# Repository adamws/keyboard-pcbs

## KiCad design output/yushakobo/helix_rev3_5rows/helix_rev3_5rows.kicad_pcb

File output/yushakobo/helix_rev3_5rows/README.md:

## yushakobo/helix_rev3_5rows

[layout](helix_rev3_5rows-kle.json) - [PCB](helix_rev3_5rows.kicad_pcb)

{:loading="lazy"}

[Open in keyboard-layout-editor](http://www.keyboard-layout-editor.com/##@@=0,0&=0,1&=0,2&=0,3&=0,4&=0,5&_x:2.25;&=5,5&=5,4&=5,3&=5,2&=5,1&_c=#aaaaaa;&=5,0;&@=1,0&_c=#cccccc;&=1,1&=1,2&=1,3&=1,4&=1,5&_x:2.25;&=6,5&=6,4&=6,3&=6,2&=6,1&_c=#aaaaaa;&=6,0;&@=2,0&_c=#cccccc;&=2,1&=2,2&=2,3&=2,4&=2,5&_x:2.25;&=7,5&=7,4&=7,3&=7,2&=7,1&=7,0;&@_c=#aaaaaa;&=3,0&_c=#cccccc;&=3,1&=3,2&=3,3&=3,4&=3,5&=3,6&_x:0.25;&=8,6&=8,5&=8,4&=8,3&=8,2&=8,1&_c=#aaaaaa;&=8,0;&@=4,0&=4,1&=4,2&=4,3&=4,4&=4,5&_c=#cccccc;&=4,6&_x:0.25;&=9,6&_c=#aaaaaa;&=9,5&=9,4&=9,3&=9,2&=9,1&=9,0)

{:loading="lazy"}

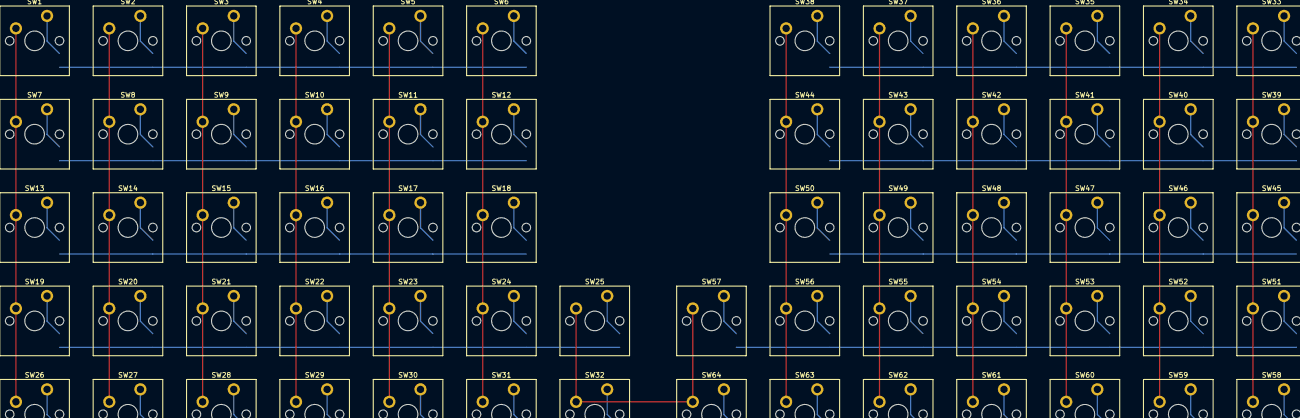
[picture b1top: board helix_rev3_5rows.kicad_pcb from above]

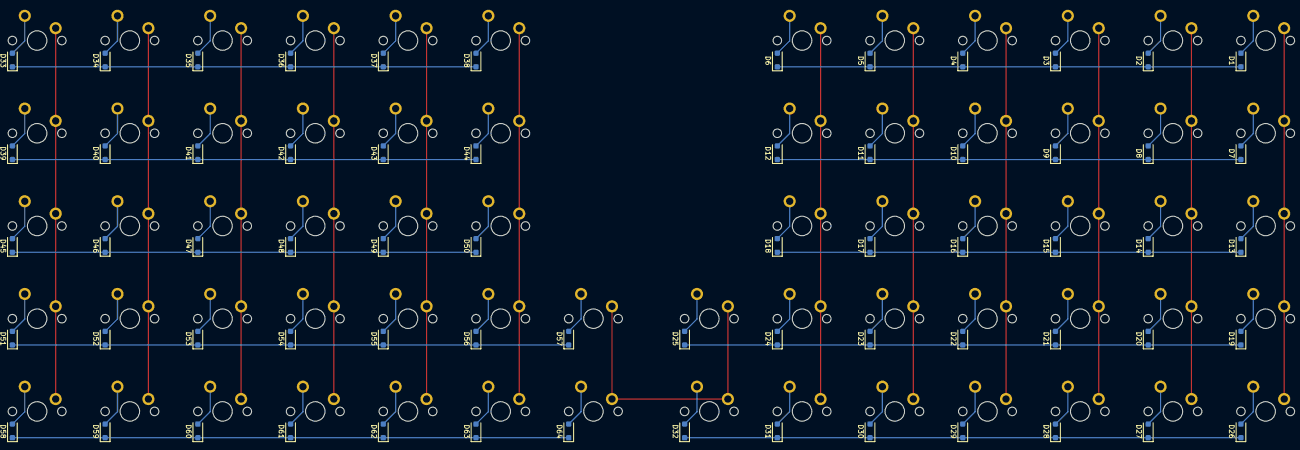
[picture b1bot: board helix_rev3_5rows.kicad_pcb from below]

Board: 2 copper layers, 128 parts (64 on the bottom side), 81 nets.

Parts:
D1, D2, D3, D4, D5, D6, D7, D8, D9, D10, D11, D12, D13, D14, D15, D16, D17, D18, D19, D20, D21, D22, D23, D24, D25, D26, D27, D28, D29, D30, D31, D32, D33, D34, D35, D36, D37, D38, D39, D40, D41, D42, D43, D44, D45, D46, D47, D48, D49, D50, D51, D52, D53, D54, D55, D56, D57, D58, D59, D60, D61, D62, D63, D64: D_SOD-123F
SW1, SW2, SW3, SW4, SW5, SW6, SW7, SW8, SW9, SW10, SW11, SW12, SW13, SW14, SW15, SW16, SW17, SW18, SW19, SW20, SW21, SW22, SW23, SW24, SW25, SW26, SW27, SW28, SW29, SW30, SW31, SW32, SW33, SW34, SW35, SW36, SW37, SW38, SW39, SW40, SW41, SW42, SW43, SW44, SW45, SW46, SW47, SW48, SW49, SW50, SW51, SW52, SW53, SW54, SW55, SW56, SW57, SW58, SW59, SW60, SW61, SW62, SW63, SW64: SW_Cherry_MX_PCB_1.00u

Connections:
COL0: SW1.1, SW7.1, SW13.1, SW19.1, SW26.1, SW33.1, SW39.1, SW45.1, SW51.1, SW58.1
COL1: SW2.1, SW8.1, SW14.1, SW20.1, SW27.1, SW34.1, SW40.1, SW46.1, SW52.1, SW59.1
COL2: SW3.1, SW9.1, SW15.1, SW21.1, SW28.1, SW35.1, SW41.1, SW47.1, SW53.1, SW60.1
COL3: SW4.1, SW10.1, SW16.1, SW22.1, SW29.1, SW36.1, SW42.1, SW48.1, SW54.1, SW61.1
COL4: SW5.1, SW11.1, SW17.1, SW23.1, SW30.1, SW37.1, SW43.1, SW49.1, SW55.1, SW62.1
COL5: SW6.1, SW12.1, SW18.1, SW24.1, SW31.1, SW38.1, SW44.1, SW50.1, SW56.1, SW63.1
COL6: SW25.1, SW32.1, SW57.1, SW64.1
unnamed: D1.2, SW1.2
unnamed: D2.2, SW2.2
unnamed: D3.2, SW3.2
unnamed: D4.2, SW4.2
unnamed: D5.2, SW5.2
unnamed: D6.2, SW6.2
unnamed: D7.2, SW7.2
unnamed: D8.2, SW8.2
unnamed: D9.2, SW9.2
unnamed: D10.2, SW10.2
unnamed: D11.2, SW11.2
unnamed: D12.2, SW12.2
unnamed: D13.2, SW13.2
unnamed: D14.2, SW14.2
unnamed: D15.2, SW15.2
unnamed: D16.2, SW16.2
unnamed: D17.2, SW17.2
unnamed: D18.2, SW18.2
unnamed: D19.2, SW19.2
unnamed: D20.2, SW20.2
unnamed: D21.2, SW21.2
unnamed: D22.2, SW22.2
unnamed: D23.2, SW23.2
unnamed: D24.2, SW24.2
unnamed: D25.2, SW25.2
unnamed: D26.2, SW26.2
unnamed: D27.2, SW27.2
unnamed: D28.2, SW28.2
unnamed: D29.2, SW29.2
unnamed: D30.2, SW30.2
unnamed: D31.2, SW31.2
unnamed: D32.2, SW32.2
unnamed: D33.2, SW33.2
unnamed: D34.2, SW34.2
unnamed: D35.2, SW35.2
unnamed: D36.2, SW36.2
unnamed: D37.2, SW37.2
unnamed: D38.2, SW38.2
unnamed: D39.2, SW39.2
unnamed: D40.2, SW40.2
unnamed: D41.2, SW41.2
unnamed: D42.2, SW42.2
unnamed: D43.2, SW43.2
unnamed: D44.2, SW44.2
unnamed: D45.2, SW45.2
unnamed: D46.2, SW46.2
unnamed: D47.2, SW47.2
unnamed: D48.2, SW48.2
unnamed: D49.2, SW49.2
unnamed: D50.2, SW50.2
unnamed: D51.2, SW51.2
unnamed: D52.2, SW52.2
unnamed: D53.2, SW53.2
unnamed: D54.2, SW54.2
unnamed: D55.2, SW55.2
unnamed: D56.2, SW56.2
unnamed: D57.2, SW57.2
unnamed: D58.2, SW58.2
unnamed: D59.2, SW59.2
unnamed: D60.2, SW60.2
unnamed: D61.2, SW61.2
unnamed: D62.2, SW62.2
unnamed: D63.2, SW63.2
unnamed: D64.2, SW64.2
ROW0: D1.1, D2.1, D3.1, D4.1, D5.1, D6.1
ROW1: D7.1, D8.1, D9.1, D10.1, D11.1, D12.1
ROW2: D13.1, D14.1, D15.1, D16.1, D17.1, D18.1
ROW3: D19.1, D20.1, D21.1, D22.1, D23.1, D24.1, D25.1
ROW4: D26.1, D27.1, D28.1, D29.1, D30.1, D31.1, D32.1
ROW5: D33.1, D34.1, D35.1, D36.1, D37.1, D38.1
ROW6: D39.1, D40.1, D41.1, D42.1, D43.1, D44.1
ROW7: D45.1, D46.1, D47.1, D48.1, D49.1, D50.1
ROW8: D51.1, D52.1, D53.1, D54.1, D55.1, D56.1, D57.1
ROW9: D58.1, D59.1, D60.1, D61.1, D62.1, D63.1, D64.1

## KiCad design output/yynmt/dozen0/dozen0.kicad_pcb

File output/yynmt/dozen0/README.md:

## yynmt/dozen0

[layout](dozen0-kle.json) - [PCB](dozen0.kicad_pcb)

{:loading="lazy"}

[Open in keyboard-layout-editor](http://www.keyboard-layout-editor.com/##@@=0,0%0A%0A%0A0,0&=0,1%0A%0A%0A0,0&=0,2%0A%0A%0A0,0&=0,3%0A%0A%0A0,0&=0,4%0A%0A%0A0,0&=0,5%0A%0A%0A0,0;&@=0,6%0A%0A%0A0,0&=0,7%0A%0A%0A0,0&=0,8%0A%0A%0A0,0&=0,9%0A%0A%0A0,0&=0,10%0A%0A%0A0,0&=0,11%0A%0A%0A0,0;&@=0,5%0A%0A%0A0,1&=0,11%0A%0A%0A0,1;&@=0,4%0A%0A%0A0,1&=0,10%0A%0A%0A0,1;&@=0,3%0A%0A%0A0,1&=0,9%0A%0A%0A0,1;&@=0,2%0A%0A%0A0,1&=0,8%0A%0A%0A0,1;&@=0,1%0A%0A%0A0,1&=0,7%0A%0A%0A0,1;&@=0,0%0A%0A%0A0,1&=0,6%0A%0A%0A0,1)

{:loading="lazy"}

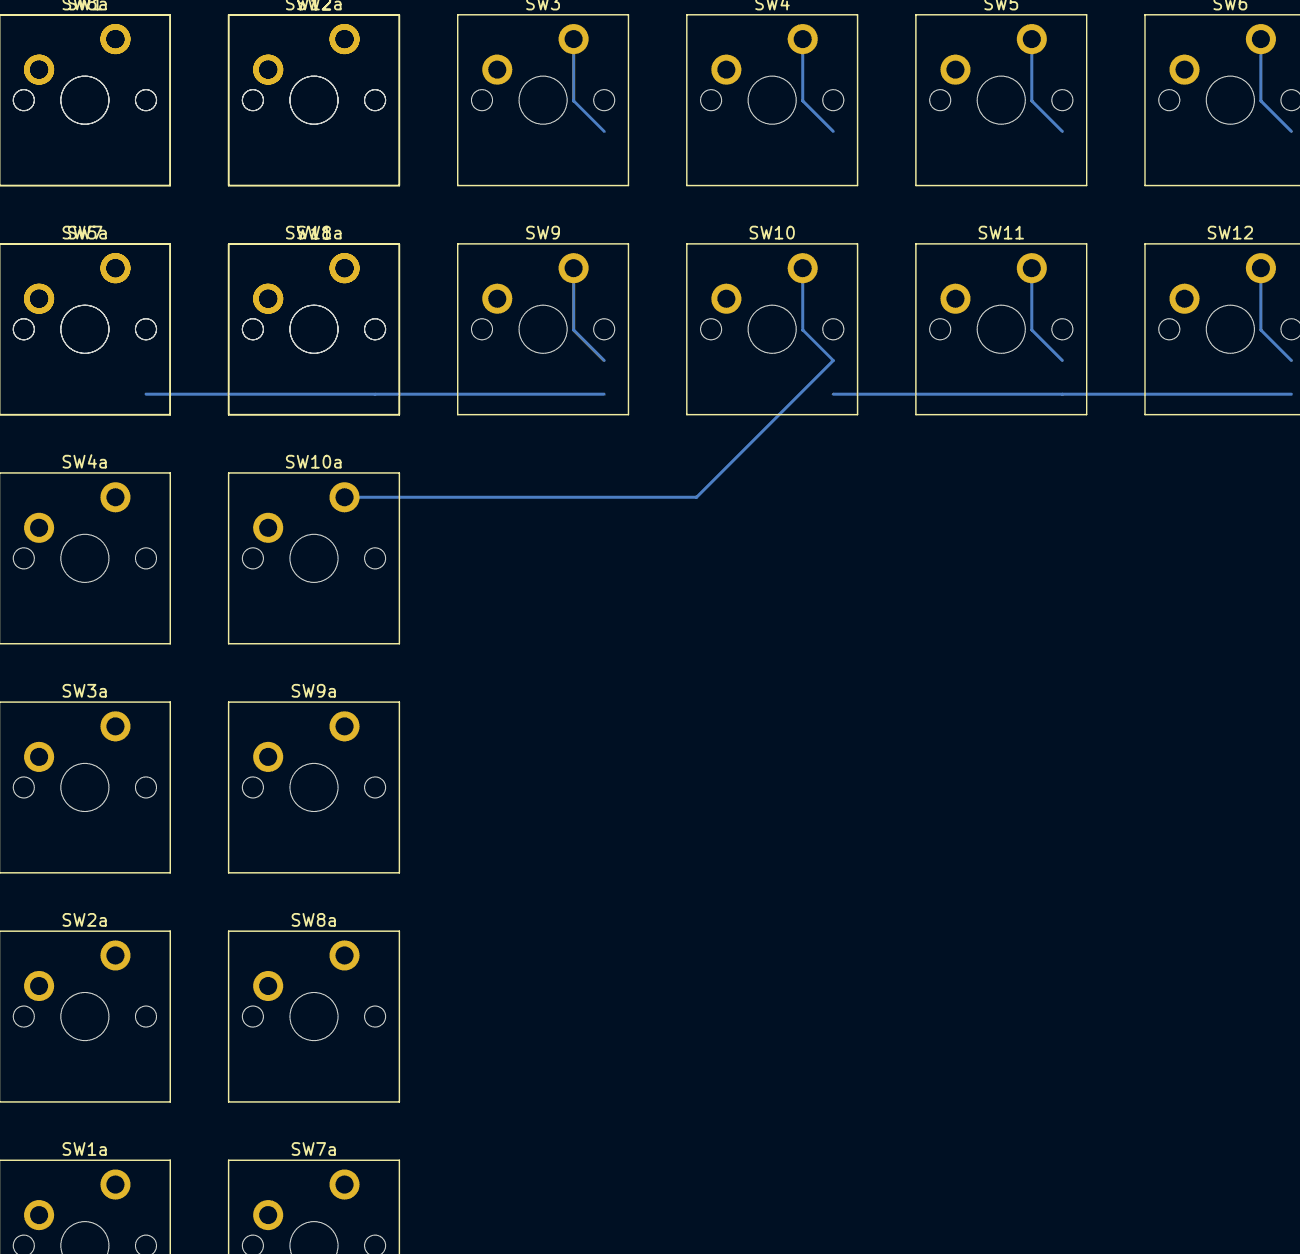
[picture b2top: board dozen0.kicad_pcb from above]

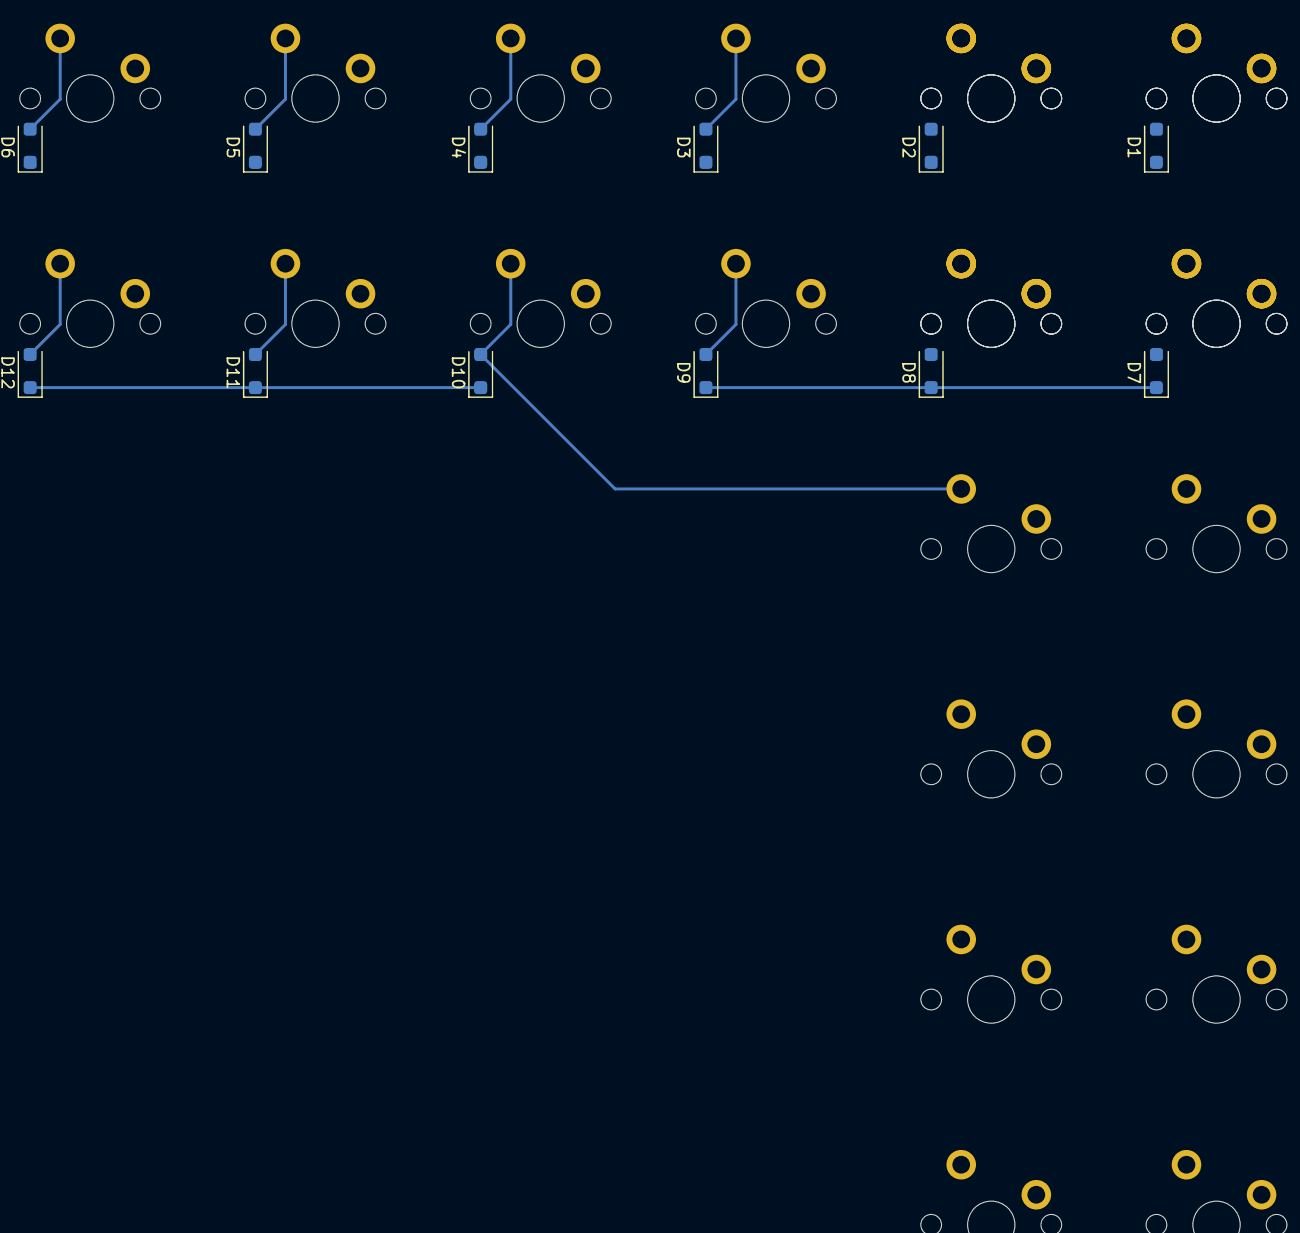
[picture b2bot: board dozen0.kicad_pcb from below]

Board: 2 copper layers, 36 parts (12 on the bottom side), 25 nets.

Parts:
D1, D2, D3, D4, D5, D6, D7, D8, D9, D10, D11, D12: D_SOD-123F
SW1, SW1a, SW2, SW2a, SW3, SW3a, SW4, SW4a, SW5, SW5a, SW6, SW6a, SW7, SW7a, SW8, SW8a, SW9, SW9a, SW10, SW10a, SW11, SW11a, SW12, SW12a: SW_Cherry_MX_PCB_1.00u

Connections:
COL0: SW1.1, SW1a.1
COL1: SW2.1, SW2a.1
COL2: SW3.1, SW3a.1
COL3: SW4.1, SW4a.1
COL4: SW5.1, SW5a.1
COL5: SW6.1, SW6a.1
COL6: SW7.1, SW7a.1
COL7: SW8.1, SW8a.1
COL8: SW9.1, SW9a.1
COL9: SW10.1, SW10a.1
COL10: SW11.1, SW11a.1
COL11: SW12.1, SW12a.1
unnamed: D1.2, SW1.2, SW1a.2
unnamed: D2.2, SW2.2, SW2a.2
unnamed: D3.2, SW3.2, SW3a.2
unnamed: D4.2, SW4.2, SW4a.2
unnamed: D5.2, SW5.2, SW5a.2
unnamed: D6.2, SW6.2, SW6a.2
unnamed: D7.2, SW7.2, SW7a.2
unnamed: D8.2, SW8.2, SW8a.2
unnamed: D9.2, SW9.2, SW9a.2
unnamed: D10.2, SW10.2, SW10a.2
unnamed: D11.2, SW11.2, SW11a.2
unnamed: D12.2, SW12.2, SW12a.2
ROW0: D1.1, D2.1, D3.1, D4.1, D5.1, D6.1, D7.1, D8.1, D9.1, D10.1, D11.1, D12.1
